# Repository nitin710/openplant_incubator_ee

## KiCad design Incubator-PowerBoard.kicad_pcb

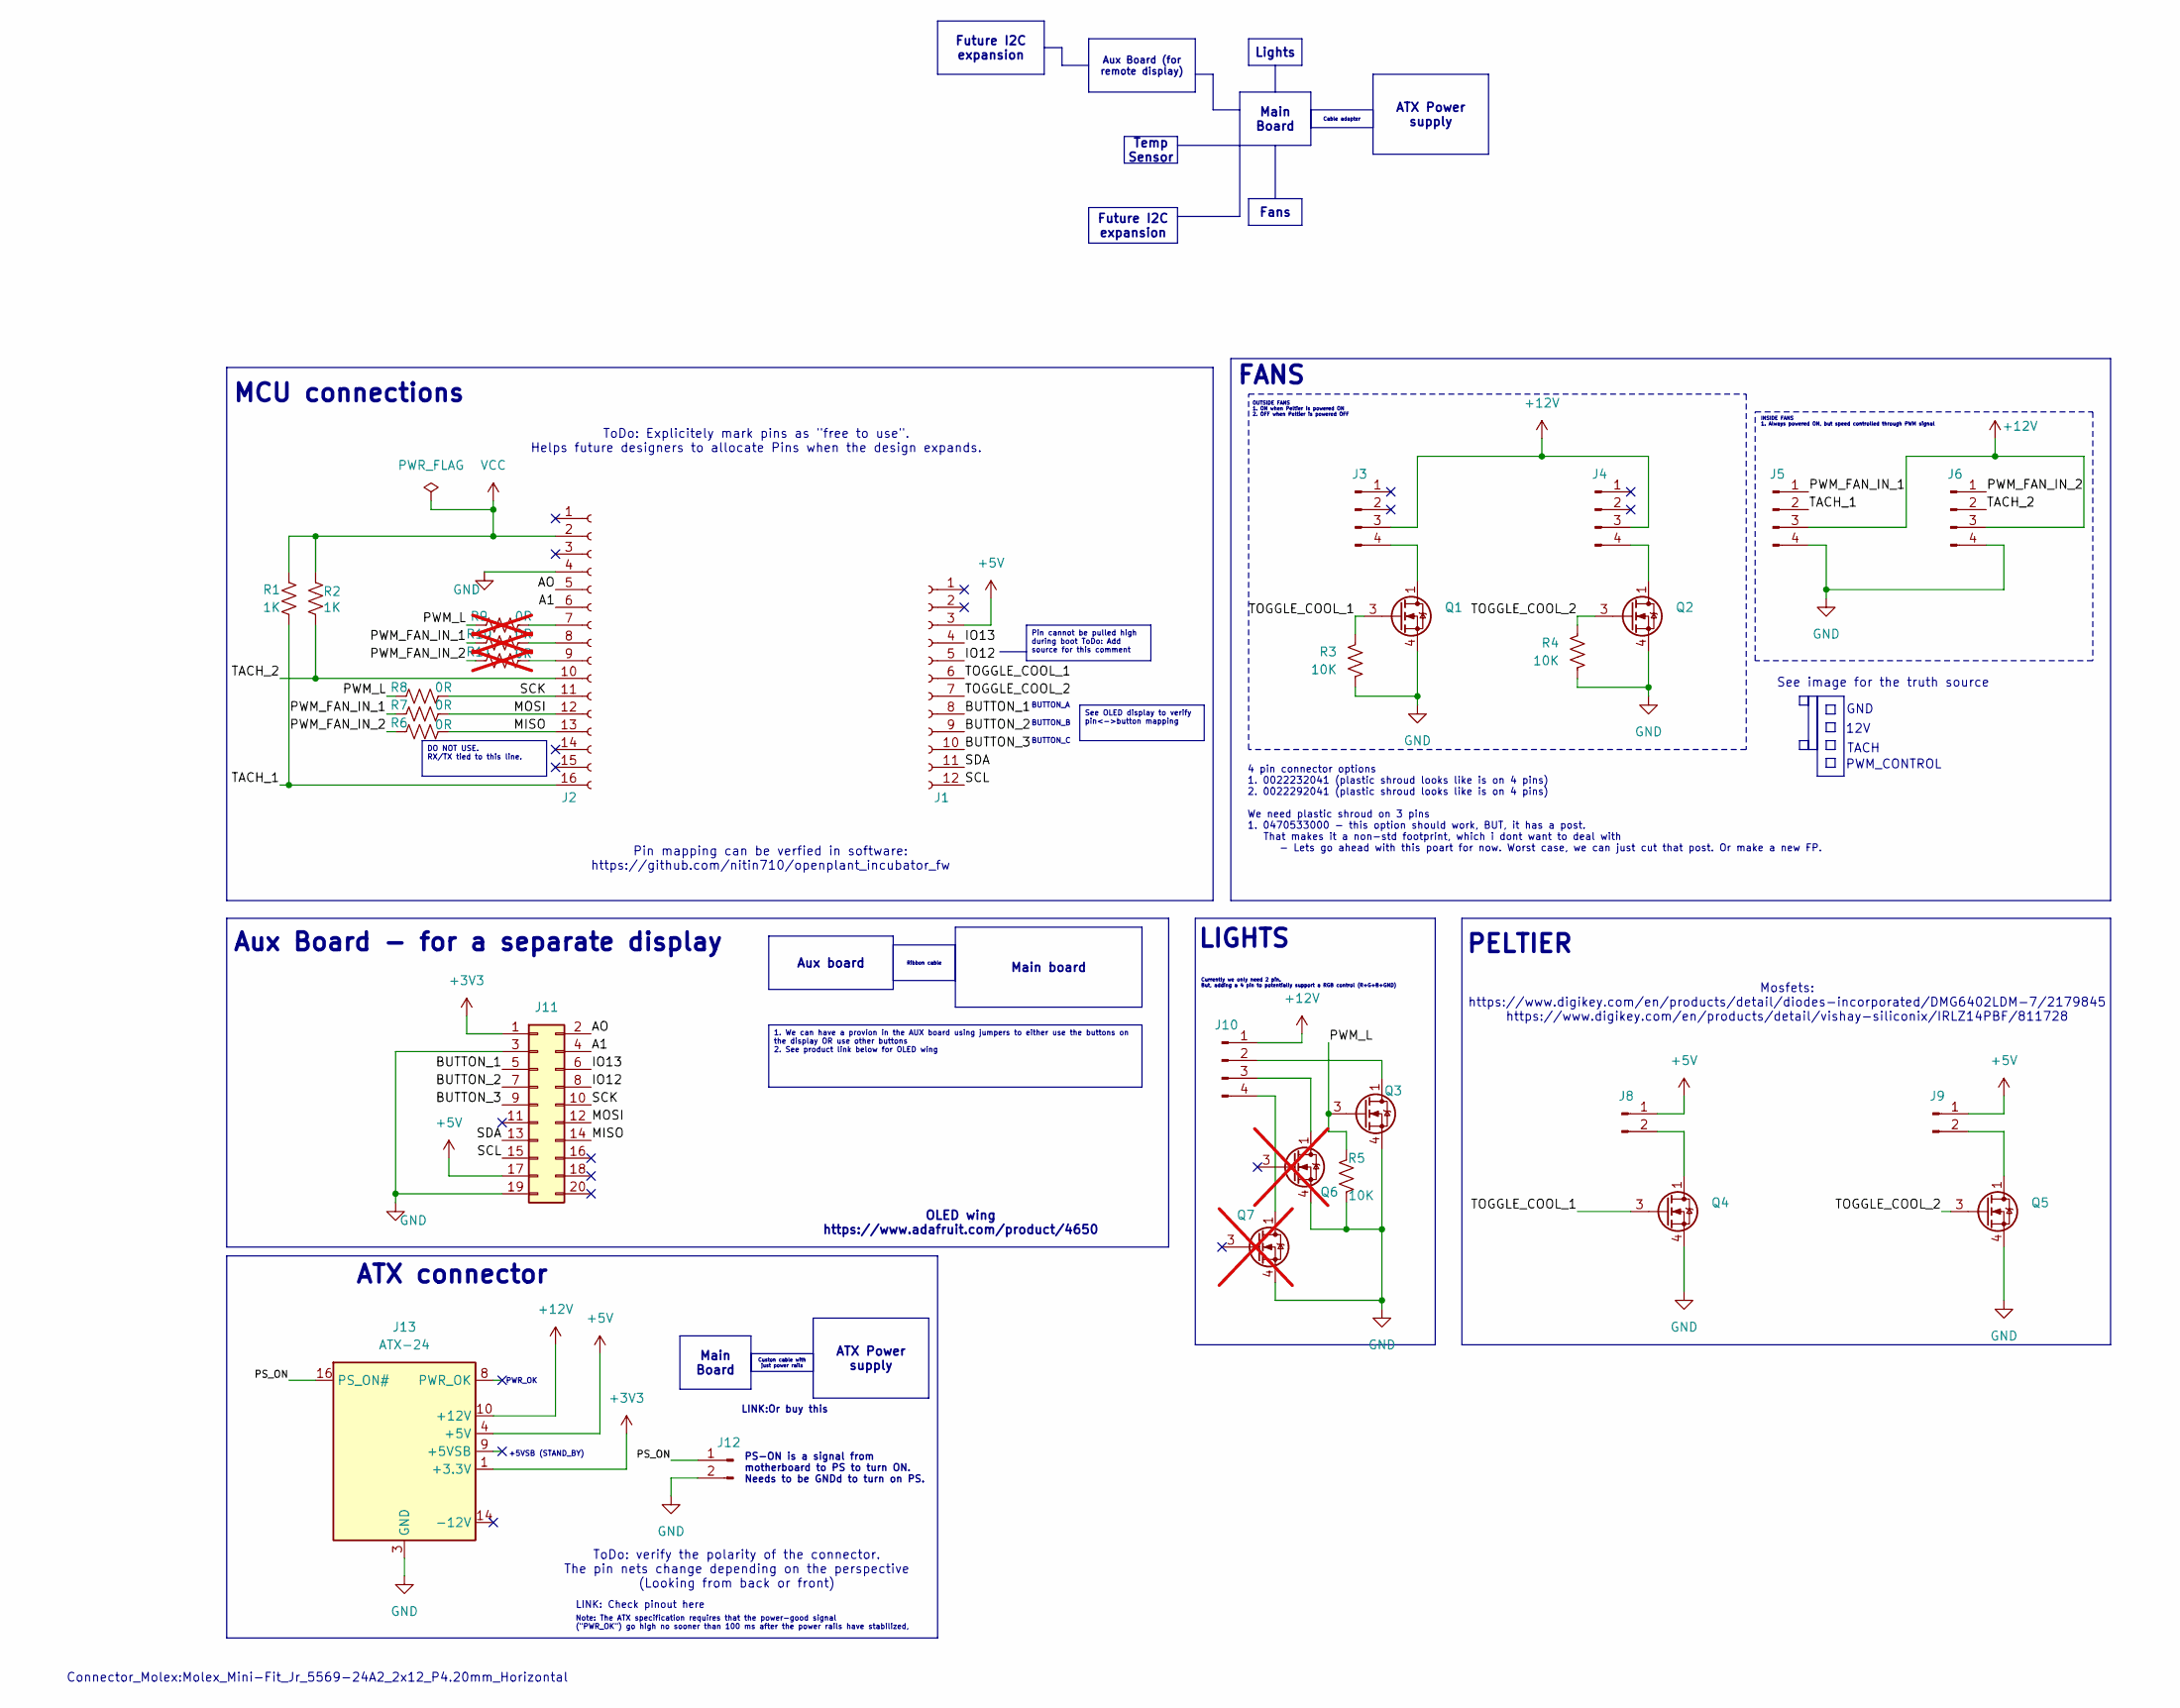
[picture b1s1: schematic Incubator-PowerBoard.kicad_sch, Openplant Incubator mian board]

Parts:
J1: Conn_01x12_Socket; PinSocket_1x12_P2.54mm_Vertical; MPN PPTC121LFBN-RC; Digikey_Part_Number S6100-ND
J2: Conn_01x16_Socket; PinSocket_1x16_P2.54mm_Vertical; MPN PPTC161LFBN-RC; Digikey_Part_Number S7014-ND
J3: OUT_FAN_1; PinHeader_1x04_P2.54mm_Vertical; MPN 61300411121; Digikey_Part_Number 732-5317-ND
J4: OUT_FAN_2; PinHeader_1x04_P2.54mm_Vertical; MPN 61300411121; Digikey_Part_Number 732-5317-ND
J5: IN_FAN_1; PinHeader_1x04_P2.54mm_Vertical; MPN 61300411121; Digikey_Part_Number 732-5317-ND
J6: IN_FAN_2; PinHeader_1x04_P2.54mm_Vertical; MPN 61300411121; Digikey_Part_Number 732-5317-ND
J8: PELTIER_1; PinHeader_1x02_P2.54mm_Vertical; MPN 61300211121; Digikey_Part_Number 732-5315-ND
J9: PELTIER_2; PinHeader_1x02_P2.54mm_Vertical; MPN 61300211121; Digikey_Part_Number 732-5315-ND
J10: LIGHTS; PinHeader_1x04_P2.54mm_Vertical; MPN 61300411121; Digikey_Part_Number 732-5317-ND
J11: Conn_02x10_Odd_Even; PinHeader_2x10_P2.54mm_Vertical
J12: Conn_01x02_Pin; PinHeader_1x02_P2.54mm_Vertical; MPN 61300211121; Digikey_Part_Number 732-5315-ND
J13: ATX-24; Molex_Mini-Fit_Jr_5569-24A2_2x12_P4.20mm_Horizontal
Q1: OUT_FAN_1; SOT-23-6; MPN DMG6402LVT-7; Digikey_Part_Number DMG6402LVT-7DICT-ND
Q2: OUT_FAN_2; SOT-23-6; MPN DMG6402LVT-7; Digikey_Part_Number DMG6402LVT-7DICT-ND
Q3: LIGHTS; SOT-23-6; MPN DMG6402LVT-7; Digikey_Part_Number DMG6402LVT-7DICT-ND
Q4: PELTIER_1; SOT-23-6; MPN DMG6402LVT-7; Digikey_Part_Number DMG6402LVT-7DICT-ND
Q5: PELTIER_2; SOT-23-6; MPN DMG6402LVT-7; Digikey_Part_Number DMG6402LVT-7DICT-ND
Q6, Q7: DMG6402LVT-7; SOT-23-6; MPN DMG6402LVT-7; Digikey_Part_Number DMG6402LVT-7DICT-ND; not fitted
R1, R2: 1K; R_1210_3225Metric; MPN CRCW12101K00JNEAIF
R3, R4, R5: 10K; R_0603_1608Metric; MPN RMCF0603JT10K0; Digikey Part Number RMCF0603JT10K0CT-ND
R6, R7, R8: 0R; R_0603_1608Metric; MPN RMCF0603ZT0R00; Digikey_Part_Number RMCF0603ZT0R00CT-ND
R9, R10, R11: 0R; R_0603_1608Metric; MPN RMCF0603ZT0R00; Digikey_Part_Number RMCF0603ZT0R00CT-ND; not fitted

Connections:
+3V3: J11.1, J13.1 (+3.3V), J13.2 (+3.3V), J13.12 (+3.3V), J13.13 (+3.3V)
+5V: J1.3, J8.1, J9.1, J11.17, J13.4 (+5V), J13.6 (+5V), J13.21 (+5V), J13.22 (+5V), J13.23 (+5V)
+12V: J3.3, J4.3, J5.3, J6.3, J10.1, J13.10 (+12V), J13.11 (+12V)
/A1: J2.6, J11.4
/AO: J2.5, J11.2
/BUTTON_1: J1.8, J11.5
/BUTTON_2: J1.9, J11.7
/BUTTON_3: J1.10, J11.9
/IO12: J1.5, J11.8
/IO13: J1.4, J11.6
/MISO: J2.13, J11.14, R6.2
/MOSI: J2.12, J11.12, R7.2
/PS_ON: J12.1, J13.16 (PS_ON#)
/PWM_FAN_IN_1: J5.1, R7.1, R10.1
/PWM_FAN_IN_2: J6.1, R6.1, R11.1
/PWM_L: Q3.3 (G), R5.1, R8.1, R9.1
/SCK: J2.11, J11.10, R8.2
/SCL: J1.12, J11.15
/SDA: J1.11, J11.13
/TACH_1: J2.16, J5.2, R1.2
/TACH_2: J2.10, J6.2, R2.2
/TOGGLE_COOL_1: J1.6, Q1.3 (G), Q4.3 (G), R3.1
/TOGGLE_COOL_2: J1.7, Q2.3 (G), Q5.3 (G), R4.1
GND: J2.4, J5.4, J6.4, J11.3, J11.19, J12.2, J13.3 (GND), J13.5 (GND), J13.7 (GND), J13.15 (GND), J13.17 (GND), J13.18 (GND), J13.19 (GND), J13.24 (GND), Q1.4 (S), Q2.4 (S), Q3.4 (S), Q4.4 (S), Q5.4 (S), Q6.4 (S), Q7.4 (S), R3.2, R4.2, R5.2
unnamed: J2.7, R9.2
unnamed: J2.8, R10.2
unnamed: J2.9, R11.2
unnamed: J3.4, Q1.1 (D), Q1.2 (D), Q1.5 (D), Q1.6 (D)
unnamed: J4.4, Q2.1 (D), Q2.2 (D), Q2.5 (D), Q2.6 (D)
unnamed: J8.2, Q4.1 (D), Q4.2 (D), Q4.5 (D), Q4.6 (D)
unnamed: J9.2, Q5.1 (D), Q5.2 (D), Q5.5 (D), Q5.6 (D)
unnamed: J10.2, Q3.1 (D), Q3.2 (D), Q3.5 (D), Q3.6 (D)
unnamed: J10.3, Q6.1 (D), Q6.2 (D), Q6.5 (D), Q6.6 (D)
unnamed: J10.4, Q7.1 (D), Q7.2 (D), Q7.5 (D), Q7.6 (D)
VCC: J2.2, R1.1, R2.1

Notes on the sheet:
Aux Board (for remote display)
Fans
ATX Power supply
DO NOT USE. RX/TX tied to this line.
See OLED display to verify pin<->button mapping
Main board
Cable adapter
Pin cannot be pulled high during boot ToDo: Add source for this comment
Lights
Future I2C expansion
Main Board
1. We can have a provion in the AUX board using jumpers to either use the buttons on the display OR use other buttons 2. See product link below for OLED wing
Ribbon cable
Custon cable with just power rails
Temp Sensor
Aux board
PELTIER
PWM_CONTROL
LINK:Or buy this
BUTTON_B
See image for the truth source
Aux Board - for a separate display
MCU connections
LINK: Check pinout here
4 pin connector options 1. 0022232041 (plastic shroud looks like is on 4 pins) 2. 0022292041 (plastic shroud looks like is on 4 pins) We need plastic shroud on 3 pins 1. 0470533000 - this option should work, BUT, it has a post. That makes it a non-std footprint, which i dont want to deal with - Let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
GND
Mosfets: https://www.digikey.com/en/products/detail/diodes-incorporated/DMG6402LDM-7/2179845 https://www.digikey.com/en/products/detail/vishay-siliconix/IRLZ14PBF/811728
BUTTON_C
ToDo: Explicitely mark pins as "free to use". Helps future designers to allocate Pins when the design expands.
OUTSIDE FANS 1. ON when Peltier is powered ON 2. OFF when Peltier is powered OFF
OLED wing https://www.adafruit.com/product/4650
Currently we only need 2 pin. But, adding a 4 pin to potentially support a RGB control (R+G+B+GND)
ATX connector
INSIDE FANS 1. Always powered ON, but speed controlled through PWM signal
Pin mapping can be verfied in software: https://github.com/nitin710/openplant_incubator_fw
ToDo: verify the polarity of the connector. The pin nets change depending on the perspective (Looking from back or front)
LIGHTS
+5VSB (STAND_BY)
BUTTON_A
FANS

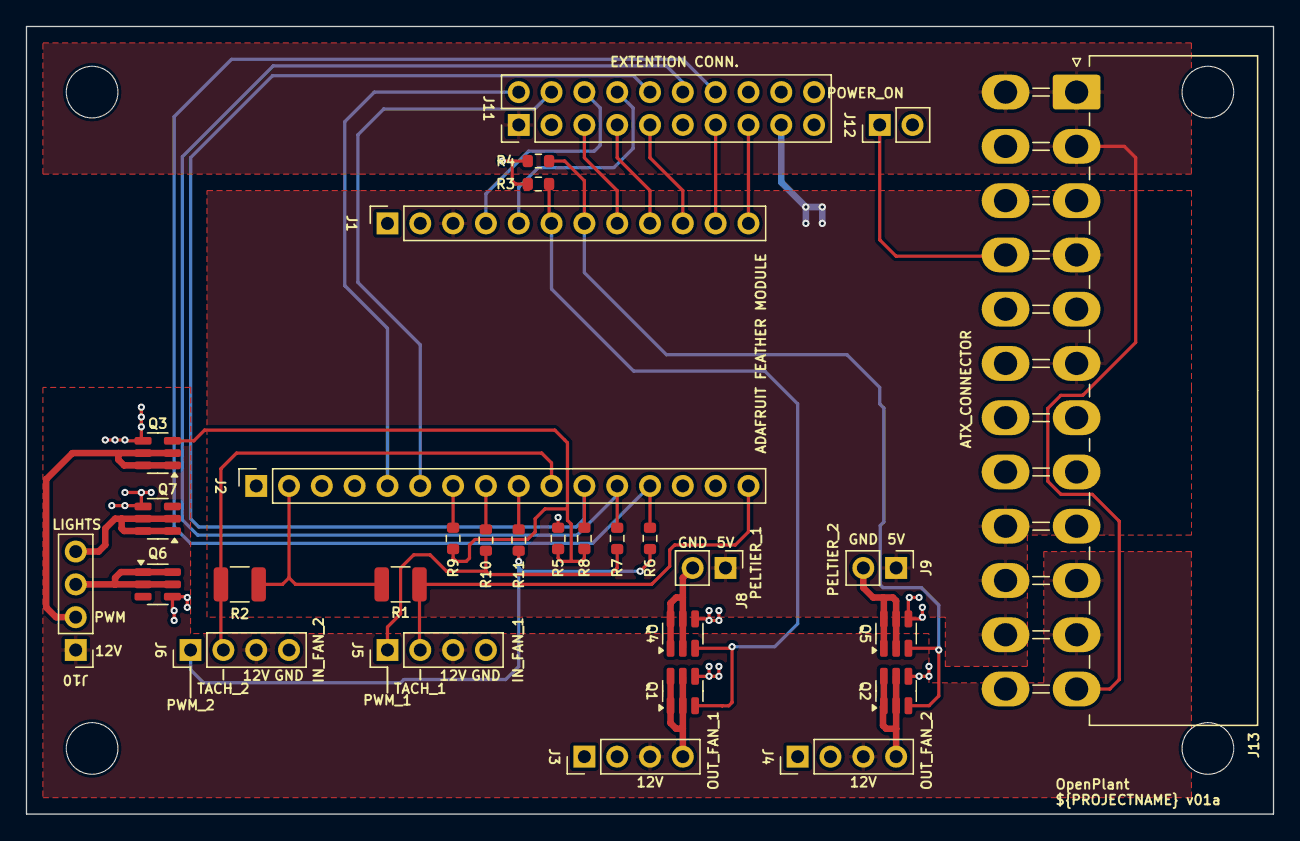
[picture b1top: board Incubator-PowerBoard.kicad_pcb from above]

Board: 2 copper layers, 96.5 x 61.0 mm, 30 parts (0 on the bottom side), 35 nets.

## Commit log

2024-03-04 adding init design files
2024-03-04 udpated comments
2024-10-19 layout complete
2024-10-21 added 3d for atx connector
2024-11-17 adding MFG files
2024-11-21 update to drc exclusion
